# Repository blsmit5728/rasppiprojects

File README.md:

rasppiprojects
==============

My Raspberry Pi Projects

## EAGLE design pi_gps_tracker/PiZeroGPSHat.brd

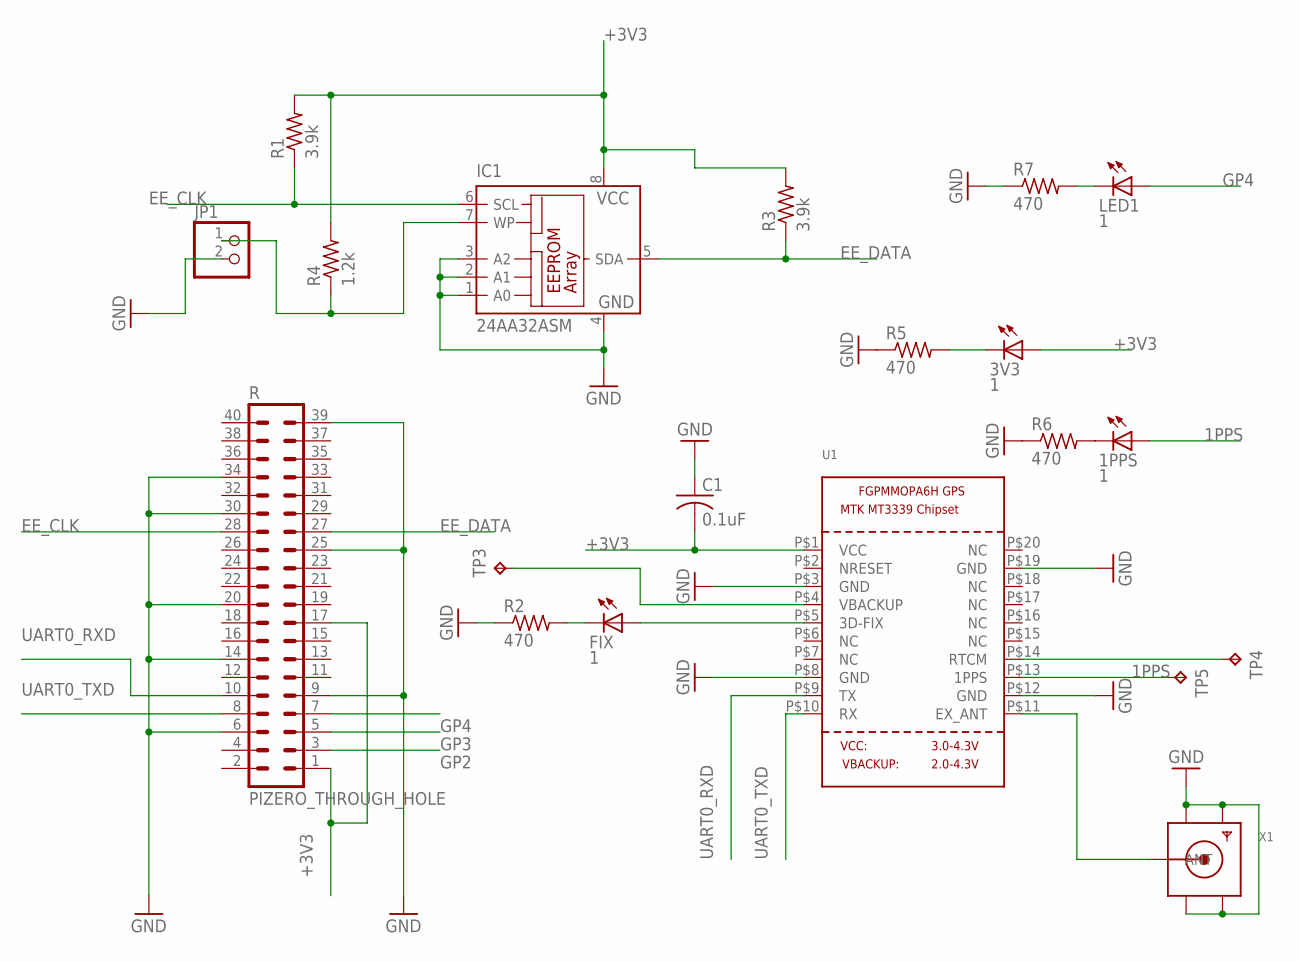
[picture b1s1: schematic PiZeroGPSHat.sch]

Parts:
1PPS, 3V3: 1; CHIPLED_0805
C1: 0.1uF; C0402
FIX: 1; CHIPLED_0805
IC1: 24AA32ASM; SO-08M
JP1: PINHD-1X2; 1X02
LED1: 1; CHIPLED_0805
R: PIZERO_THROUGH_HOLE; PIZERO_THOUGH_HOLE
R1, R3: 3.9k; R0402
R2, R5, R6, R7: 470; R0402
R4: 1.2k; R0402
TP3, TP4, TP5: TPB1,27; B1,27
U1: GPS_FGPMMOPA6H; FGPMMOPA6H
X1: SMACONNECTOR; SMA90_DIP

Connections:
1PPS: 1PPS.A, TP5.TP, U1.P$13 (1PPS)
+3V3: 3V3.A, C1.2, IC1.8 (VCC), R.1, R.17, R1.2, R3.2, R4.2, U1.P$1 (VCC)
EE_CLK: IC1.6 (SCL), R.28, R1.1
EE_DATA: IC1.5 (SDA), R.27, R3.1
GND: C1.1, IC1.1 (A0), IC1.2 (A1), IC1.3 (A2), IC1.4 (GND), JP1.2, R.6, R.9, R.14, R.20, R.25, R.30, R.34, R.39, R2.1, R5.1, R6.1, R7.1, U1.P$3 (GND), U1.P$8 (GND), U1.P$12 (GND), U1.P$19 (GND), X1.GND1, X1.GND2, X1.GND3, X1.GND4
GP2: R.3
GP3: R.5
GP4: LED1.A, R.7
unnamed: FIX.A, U1.P$5 (3D-FIX)
unnamed: FIX.C, R2.2
unnamed: LED1.C, R7.2
unnamed: TP4.TP, U1.P$14 (RTCM)
unnamed: TP3.TP, U1.P$4 (VBACKUP)
unnamed: U1.P$11 (EX_ANT), X1.ANTENNA (ANT)
unnamed: 3V3.C, R5.2
unnamed: 1PPS.C, R6.2
UART0_RXD: R.10, U1.P$9 (TX)
UART0_TXD: R.8, U1.P$10 (RX)
WP: IC1.7 (WP), JP1.1, R4.1

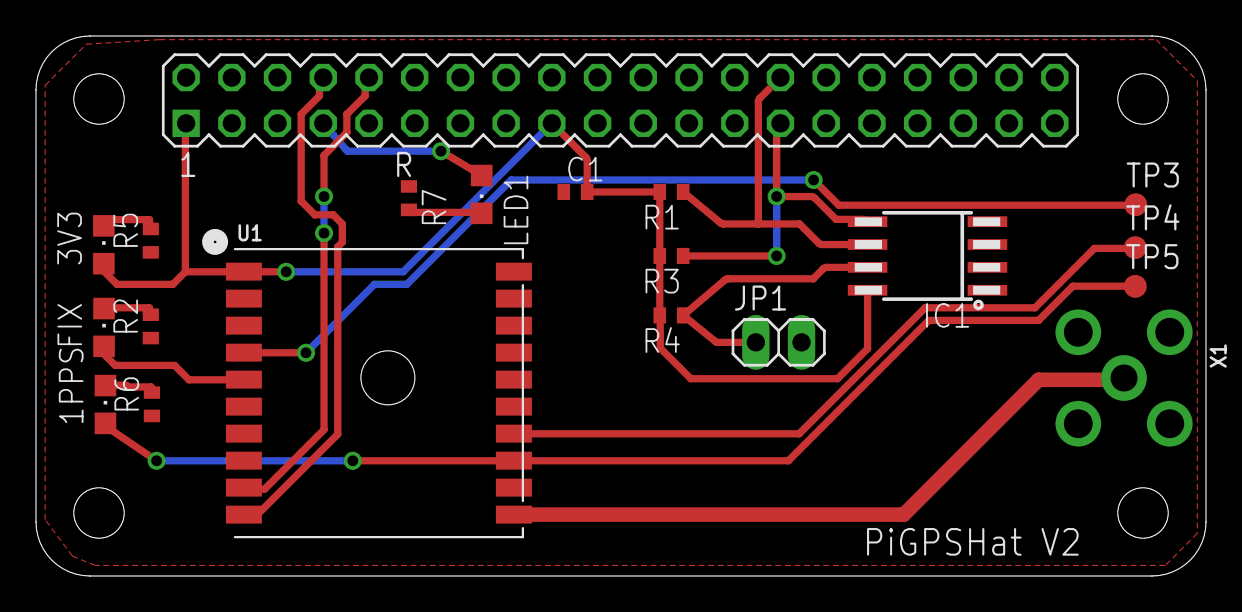
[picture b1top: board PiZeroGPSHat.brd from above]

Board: 2 copper layers, 65.0 x 30.0 mm, 20 parts (0 on the bottom side), 17 nets.

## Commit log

2012-11-24 Adding the weather station code for my raspberry pi
2012-11-25 added dew_pt and editing file.
2012-11-25 fixed the str methods
2012-11-25 added hour
2012-11-25 changed to append
2012-11-29 Added the plotting script to git
2012-12-13 Adding new file, and modified the gnu plot script
2013-01-06 Modified the gnuplot script
2013-01-27 Not sure of changes?
2013-04-03 Modifying to take out the stale data paths
2013-05-08 Modified something, forget what, and added some new files
2013-05-08 Adding the beaglebone temp reading
2013-05-14 New files for the weather station
2013-05-14 Added gitignore
2016-03-08 Adding the PiZeroGPSHat to this repo.
2016-03-08 Adding the PiZero covers to the repo.
2016-03-15 Added Jumper to the WP pins. Also fixed the SCAD to use a smaller standoff.
2016-03-15 Added Jumper to WP.
2016-03-18 Added a tty script to get the serial in a mode we can read it.
2016-03-19 V2 of the GPS hat to add LEDs for status indicators
2016-03-19 Adding the gps app to the repo
2016-03-19 Adding ignore of the tmp brd files
2016-03-19 V3 moved all the LEDs to the same location.
2016-03-21 Adding new case
2016-04-04 New Board and SCAD
2016-08-25 Adding the garage_door.py project to the repo.
2017-04-26 Added the Fritxzing Object for the Full project box.
2017-05-02 Adding the GPS full case to the project.
    So far I am just making the modules that I will later put together to make the full project.
2017-05-02 Got the platform for the powerboost module done
2017-05-03 Added git ignore. Added OLED info and updated case.
2017-05-08 working to move the case to a building stlye with walls
2017-05-08 New Layout
    Laid out all pieces just need to find a way to connect two halves.
2017-05-09 Final Version
    Now have standoffs and counter sinks on the lid.
2017-05-11 Updating with new standoffs...
2017-05-13 Woohoo
    Got a nice final product for production!
2017-05-15 Made sure top had 2.125mm width for walls.
2017-05-21 Adding infostation project for GA house
2017-05-26 copy added
2017-05-26 rounded rect
